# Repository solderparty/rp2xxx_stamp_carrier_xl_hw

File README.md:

# The RP2xxx Stamp Carrier Board XL

The RP2xxx Stamp Carrier XL, as the (somewhat long) name suggests, supports all the RP2-based Stamp boards. The Mega/Due form-factor ensures compatbility with many shields, including Uno ones. The wide range of connectors on the Carrier makes it a fully-fledged RP2xxx dev board.

The Carrier comes with a combo 3-in-1 SMD/TH/FlexyPin Stamp footprint, you can solder the Stamp directly to the Carrier, use 2mm pin headers + sockets to be able to plug it in and out, or use [FlexyPins](https://docs.solder.party/flexypin) to pop the Stamp in and out of the Carrier would soldering the Stamp. This way the Carrier also acts as a great Stamp flashing and testing jig. Check out the [Assembly Options](https://docs.solder.party/rp2xxx-stamp-carrier-xl/assembly_options) page for more details.

The board can be powered from the LiPo, over USB, or with a DC jack.

By using the RP2040 Stamp Carrier, you get everything that comes with the Stamp plus:

- USB Host and Device connectors with a toggle switch
- microSD socket
- Micro HDMI-shaped connector, connected to the HSTX peripheral
- SWD JST connector, compatible with the Raspberry Pi Pico Probe
- UART JST connector, compatible with the Raspberry Pi Pico Probe
- Qwiic connector
- 3.7/4.2V LiPo connector
- two user buttons
- PMOD header
- USR LED
- Power (3.3V) LED
- DC Jack

The DC Jack input is center-positive and supports voltages in the range of 7-12V. If you have the LiPo and either DC or USB connected, the battery will begin charging.

As mentioned above, the Carrier follows the Mega/Due/Uno shield pinout, making it compatible with a large ecosystem of shields, as long as they work on 3.3V IOs. **The pins are not 5V-tolerant**.

The CircuitPython firmware for the Stamps comes with a built-in board file for the Carrier, you can access it using `import stamp_carrier_board_xl as board`. After that, you can access all the Carrier pins and interfaces like you would with any other CPY board.

# Links

For more information visit https://rp2xxx-stamp-carrier-xl.solder.party/

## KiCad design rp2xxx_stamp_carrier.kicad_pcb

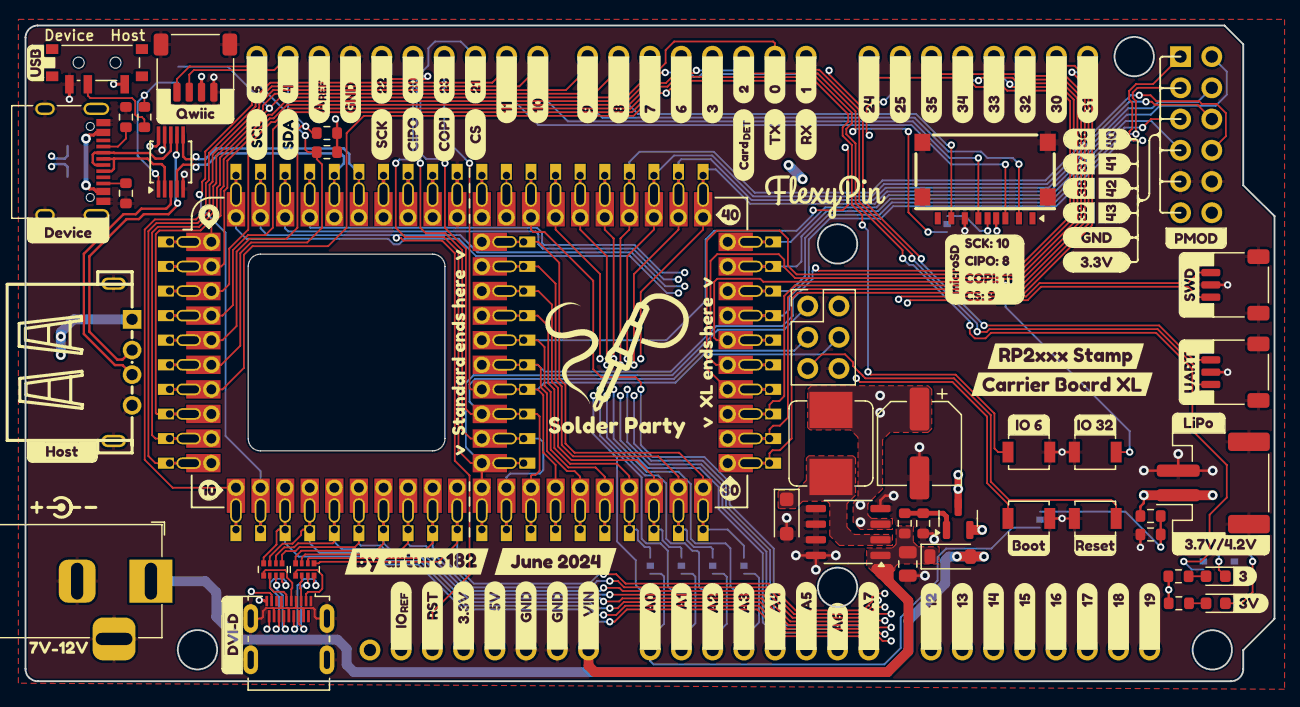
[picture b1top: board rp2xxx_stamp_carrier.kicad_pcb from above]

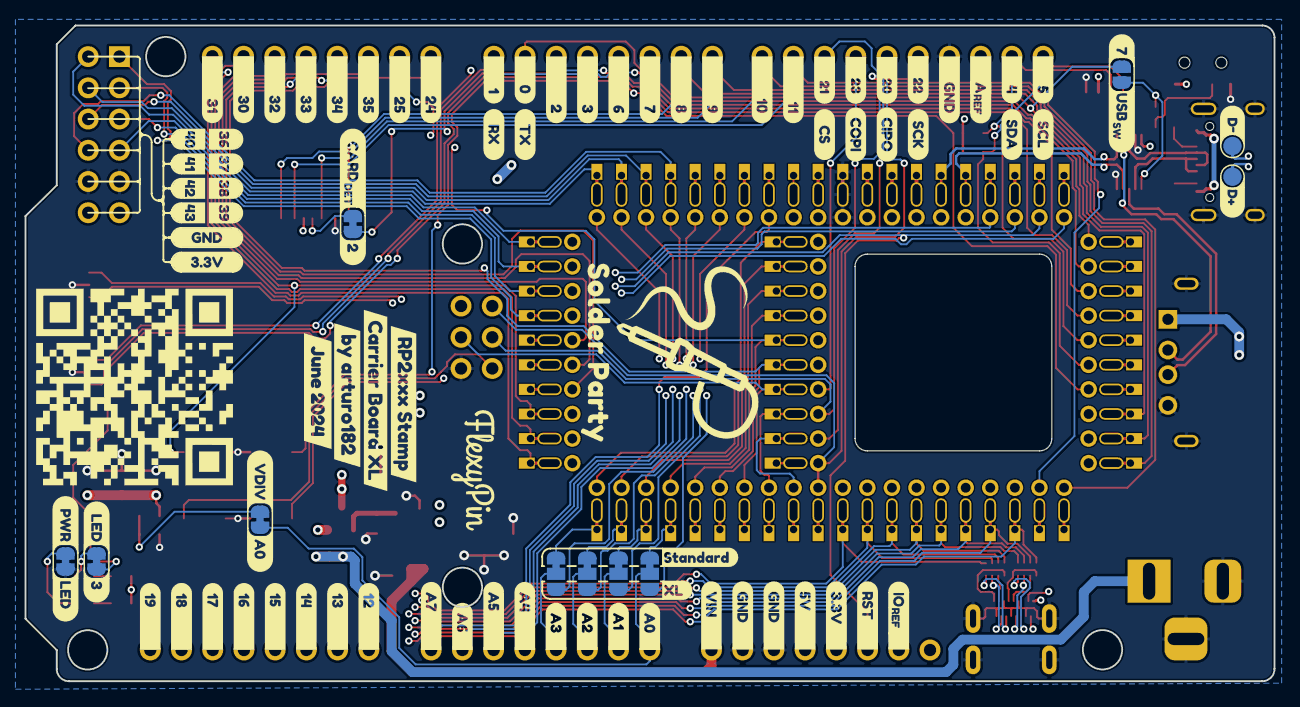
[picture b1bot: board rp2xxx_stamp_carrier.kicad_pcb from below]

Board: 4 copper layers, 101.6 x 53.3 mm, 255 parts (105 on the bottom side), 89 nets.

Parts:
C1: 22uF 25V; C_0805_2012Metric
C2: 100uF 25V; CP_Elec_6.3x4.9
D1: LED_USR; LED_0603_1608Metric
D2: 1N5819W; D_SOD-123
D3: DSS34; D_SOD-123F
D4: LED_PWR; LED_0603_1608Metric
J1: Conn_Qwiic; JST_SH_SM04B-SRSS-TB_1x04-1MP_P1.00mm_Horizontal
J2: Conn_Pi_SWD; JST_SH_SM03B-SRSS-TB_1x03-1MP_P1.00mm_Horizontal
J3: Conn_Pi_UART; JST_SH_SM03B-SRSS-TB_1x03-1MP_P1.00mm_Horizontal
J4: Conn_Batt; JST_PH_S2B-PH-SM4-TB_1x02-1MP_P2.00mm_Horizontal
J5: Barrel_Jack; BarrelJack_Horizontal
J6: DVI-D_Micro; HDMI_Micro-D_Molex_46765-1x01
J8: Conn_PMOD; PinSocket_2x06_P2.54mm_Vertical
J9, J12, J14, J15, J16: Conn_01x08; PinSocket_1x08_P2.54mm_Vertical
J10: Conn_01x10; PinSocket_1x10_P2.54mm_Vertical
J11: microSD; XUNPU_TF-123-ARP9Hxx
J13: Conn_SPI; PinHeader_2x03_P2.54mm_Vertical
J17: USB_C_Receptacle_USB2.0; USB_C_Receptacle_XKB_U262-16XN-4BVC11
J18: USB_A; USB_A_Receptacle_908-261A1011D10100
JP1: JP_VDIV; SolderJumper-2_P1.3mm_Bridged_RoundedPad1.0x1.5mm
JP2: JP_LED_USR; SolderJumper-2_P1.3mm_Bridged_RoundedPad1.0x1.5mm
JP3: JP_SD_DET; SolderJumper-2_P1.3mm_Bridged_RoundedPad1.0x1.5mm
JP4: JP_USB_SWITCH; SolderJumper-2_P1.3mm_Open_RoundedPad1.0x1.5mm
JP9: JP_LED_PWR; SolderJumper-2_P1.3mm_Bridged_RoundedPad1.0x1.5mm
JP10: SJ_A0; SolderJumper-3_P1.3mm_Bridged12_RoundedPad1.0x1.5mm
JP11: SJ_A1; SolderJumper-3_P1.3mm_Bridged12_RoundedPad1.0x1.5mm
JP12: SJ_A2; SolderJumper-3_P1.3mm_Bridged12_RoundedPad1.0x1.5mm
JP13: SJ_A3; SolderJumper-3_P1.3mm_Bridged12_RoundedPad1.0x1.5mm
L1: 47uH; L_Bourns_SRP7028A_7.3x6.6mm
Q1: DMG3415U-7; SOT-23
R1, R8: 1K; R_0603_1608Metric
R2, R3: 4.7K; R_0603_1608Metric
R4, R5, R6, R7, R11: 100K; R_0603_1608Metric
R9, R10: 5.1K; R_0603_1608Metric
RN1, RN2: 270R; R_Array_Convex_4x0402
SW1: BTN_RESET; SW_SPST_B3U-1000P
SW2: BTN_BOOTSEL; SW_SPST_B3U-1000P
SW3: SW_USB; SW_SPDT_PCM12
SW4: BTN_USR1; SW_SPST_B3U-1000P
SW5: BTN_USR2; SW_SPST_B3U-1000P
TP1: TP_USB_D+; TestPoint_Pad_D1.5mm
TP2: TP_USB_D-; TestPoint_Pad_D1.5mm
U1: XL1509-5.0; SOP-8_3.9x4.9mm_P1.27mm
U2: MSUSB30; MSOP-10_3x3mm_P0.5mm
U3: rp2xxx_Stamp_XL; RP2xx_Stamp_FlexyPin
kibuzzard-65DA3D92, kibuzzard-65DA3D92#2: G***; kibuzzard-65DA3D92
kibuzzard-65DA3D96, kibuzzard-65DA3D96#2: G***; kibuzzard-65DA3D96
kibuzzard-65DA3DCF: G***; kibuzzard-65DA3DCF
kibuzzard-65DA3ED0: G***; kibuzzard-65DA3ED0
kibuzzard-65DA3EE8, kibuzzard-65DA3EE8#2, kibuzzard-65DA3EE8#3, kibuzzard-65DA3EE8#4: G***; kibuzzard-65DA3EE8
kibuzzard-65DA13F9: G***; kibuzzard-65DA13F9
kibuzzard-65DA35ED: G***; kibuzzard-65DA35ED
kibuzzard-65DA43E4: G***; kibuzzard-65DA43E4
kibuzzard-65DA140C: G***; kibuzzard-65DA140C
kibuzzard-65DA141A: G***; kibuzzard-65DA141A
kibuzzard-65DA141E: G***; kibuzzard-65DA141E
kibuzzard-65DA143D: G***; kibuzzard-65DA143D
kibuzzard-65DA144D: G***; kibuzzard-65DA144D
kibuzzard-65DA145C: G***; kibuzzard-65DA145C
kibuzzard-65DA146D: G***; kibuzzard-65DA146D
kibuzzard-65DA148C: G***; kibuzzard-65DA148C
kibuzzard-65DA150C: G***; kibuzzard-65DA150C
kibuzzard-65DA150E: G***; kibuzzard-65DA150E
kibuzzard-65DA445F, kibuzzard-65DA445F#2: G***; kibuzzard-65DA445F
kibuzzard-65DA451B: G***; kibuzzard-65DA451B
kibuzzard-65DA451F: G***; kibuzzard-65DA451F
kibuzzard-65DA1408: G***; kibuzzard-65DA1408
kibuzzard-65DA1410: G***; kibuzzard-65DA1410
kibuzzard-65DA1413: G***; kibuzzard-65DA1413
kibuzzard-65DA1417: G***; kibuzzard-65DA1417
kibuzzard-65DA1440: G***; kibuzzard-65DA1440
kibuzzard-65DA1442: G***; kibuzzard-65DA1442
kibuzzard-65DA1448: G***; kibuzzard-65DA1448
kibuzzard-65DA1450: G***; kibuzzard-65DA1450
kibuzzard-65DA1453: G***; kibuzzard-65DA1453
kibuzzard-65DA1457: G***; kibuzzard-65DA1457
kibuzzard-65DA1460: G***; kibuzzard-65DA1460
kibuzzard-65DA1463: G***; kibuzzard-65DA1463
kibuzzard-65DA1466: G***; kibuzzard-65DA1466
kibuzzard-65DA1469: G***; kibuzzard-65DA1469
kibuzzard-65DA1470: G***; kibuzzard-65DA1470
kibuzzard-65DA1473: G***; kibuzzard-65DA1473
kibuzzard-65DA1483: G***; kibuzzard-65DA1483
kibuzzard-65DA1486: G***; kibuzzard-65DA1486
kibuzzard-65DA1492: G***; kibuzzard-65DA1492
kibuzzard-65DA1508: G***; kibuzzard-65DA1508
kibuzzard-65DA1511: G***; kibuzzard-65DA1511
kibuzzard-65DA1514: G***; kibuzzard-65DA1514
kibuzzard-65DA1517: G***; kibuzzard-65DA1517
kibuzzard-65DA4352: G***; kibuzzard-65DA4352
kibuzzard-65DA4391, kibuzzard-65DA4391#2, kibuzzard-65DA4391#3, kibuzzard-65DA4391#4: G***; kibuzzard-65DA4391
kibuzzard-65DA4455, kibuzzard-65DA4455#2: G***; kibuzzard-65DA4455
kibuzzard-65DA4463, kibuzzard-65DA4463#2: G***; kibuzzard-65DA4463
kibuzzard-65DA4468, kibuzzard-65DA4468#2: G***; kibuzzard-65DA4468
kibuzzard-65DA4513, kibuzzard-65DA4513#2: G***; kibuzzard-65DA4513
kibuzzard-65DA4517, kibuzzard-65DA4517#2: G***; kibuzzard-65DA4517
kibuzzard-65DB6F6F: G***; kibuzzard-65DB6F6F
kibuzzard-65DB8C3D: G***; kibuzzard-65DB8C3D
kibuzzard-65DB8C4A: G***; kibuzzard-65DB8C4A
kibuzzard-65DB8C5D: G***; kibuzzard-65DB8C5D
kibuzzard-65DB8C6C: G***; kibuzzard-65DB8C6C
kibuzzard-65DB8C35: G***; kibuzzard-65DB8C35
kibuzzard-65DB8C43: G***; kibuzzard-65DB8C43
kibuzzard-65DB8C55: G***; kibuzzard-65DB8C55
kibuzzard-65DB8C65: G***; kibuzzard-65DB8C65
kibuzzard-65DB8CB7: G***; kibuzzard-65DB8CB7
kibuzzard-65DB8EB0: G***; kibuzzard-65DB8EB0
kibuzzard-65DB9A5B: G***; kibuzzard-65DB9A5B
kibuzzard-65DB9AC9: G***; kibuzzard-65DB9AC9
kibuzzard-65DB9ADE: G***; kibuzzard-65DB9ADE
kibuzzard-65DB9BDD: G***; kibuzzard-65DB9BDD
kibuzzard-65DB9C6E: G***; kibuzzard-65DB9C6E
kibuzzard-65DB9FCE: G***; kibuzzard-65DB9FCE
kibuzzard-65DB9FED: G***; kibuzzard-65DB9FED
kibuzzard-65DB88A1: G***; kibuzzard-65DB88A1
kibuzzard-65DB90A8: G***; kibuzzard-65DB90A8
kibuzzard-65DB90AF: G***; kibuzzard-65DB90AF
kibuzzard-65DB90B6: G***; kibuzzard-65DB90B6
kibuzzard-65DB90CA: G***; kibuzzard-65DB90CA
kibuzzard-65DB92A0: G***; kibuzzard-65DB92A0
kibuzzard-65DB92A7: G***; kibuzzard-65DB92A7
kibuzzard-65DB92AF: G***; kibuzzard-65DB92AF
kibuzzard-65DB92BE: G***; kibuzzard-65DB92BE
kibuzzard-65DB92C6: G***; kibuzzard-65DB92C6
kibuzzard-65DB92CE: G***; kibuzzard-65DB92CE
kibuzzard-65DB92F8: G***; kibuzzard-65DB92F8
kibuzzard-65DB97A1: G***; kibuzzard-65DB97A1
kibuzzard-65DB97F6: G***; kibuzzard-65DB97F6
kibuzzard-65DB876F: G***; kibuzzard-65DB876F
kibuzzard-65DB884E: G***; kibuzzard-65DB884E
kibuzzard-65DB908D: G***; kibuzzard-65DB908D
kibuzzard-65DB909F: G***; kibuzzard-65DB909F
kibuzzard-65DB928A: G***; kibuzzard-65DB928A
kibuzzard-65DB931B: G***; kibuzzard-65DB931B
kibuzzard-65DB932B: G***; kibuzzard-65DB932B
kibuzzard-65DB8732: G***; kibuzzard-65DB8732
kibuzzard-65DB8845: G***; kibuzzard-65DB8845
kibuzzard-65DB8856: G***; kibuzzard-65DB8856
kibuzzard-65DB8860: G***; kibuzzard-65DB8860
kibuzzard-65DB9086: G***; kibuzzard-65DB9086
kibuzzard-65DB9096: G***; kibuzzard-65DB9096
kibuzzard-65DB9291: G***; kibuzzard-65DB9291
kibuzzard-65DB9299: G***; kibuzzard-65DB9299
kibuzzard-65DB9324: G***; kibuzzard-65DB9324
kibuzzard-65DBA05E: G***; kibuzzard-65DBA05E
kibuzzard-65DBA5ED: G***; kibuzzard-65DBA5ED
kibuzzard-65DBA047: G***; kibuzzard-65DBA047
kibuzzard-65DBA204: G***; kibuzzard-65DBA204
kibuzzard-65DBAB3B: G***; kibuzzard-65DBAB3B
kibuzzard-65DBAB4B: G***; kibuzzard-65DBAB4B
kibuzzard-65DBAB8B: G***; kibuzzard-65DBAB8B
kibuzzard-65DBAE3B: G***; kibuzzard-65DBAE3B
kibuzzard-65DBAE3E: G***; kibuzzard-65DBAE3E
kibuzzard-65DBAE42: G***; kibuzzard-65DBAE42
kibuzzard-65DBAE46: G***; kibuzzard-65DBAE46
kibuzzard-65DBAFC4: G***; kibuzzard-65DBAFC4
kibuzzard-65DBB0B8: G***; kibuzzard-65DBB0B8
kibuzzard-65DBB1B5: G***; kibuzzard-65DBB1B5
kibuzzard-65DBB3A0: G***; kibuzzard-65DBB3A0
kibuzzard-65DBB5CC: G***; kibuzzard-65DBB5CC
kibuzzard-65DBB07F: G***; kibuzzard-65DBB07F
kibuzzard-65DBB7FE: G***; kibuzzard-65DBB7FE
kibuzzard-65DBB28B: G***; kibuzzard-65DBB28B
kibuzzard-65DBB461: G***; kibuzzard-65DBB461
kibuzzard-65DBB727: G***; kibuzzard-65DBB727
kibuzzard-65DBBE17, kibuzzard-65DBBE17#2: G***; kibuzzard-65DBBE17
kibuzzard-65DBBE25, kibuzzard-65DBBE25#2: G***; kibuzzard-65DBBE25
kibuzzard-65DBBE65, kibuzzard-65DBBE65#2: G***; kibuzzard-65DBBE65
kibuzzard-65DBC04C: G***; kibuzzard-65DBC04C
kibuzzard-65DBC042: G***; kibuzzard-65DBC042
kibuzzard-65DBC046: G***; kibuzzard-65DBC046
kibuzzard-65DBC049: G***; kibuzzard-65DBC049
kibuzzard-65DBC50C: G***; kibuzzard-65DBC50C
kibuzzard-65DBC86E: G***; kibuzzard-65DBC86E
kibuzzard-65DBC416: G***; kibuzzard-65DBC416
kibuzzard-65DBC874: G***; kibuzzard-65DBC874
kibuzzard-65DBD3AD: G***; kibuzzard-65DBD3AD
kibuzzard-65DBD7D2, kibuzzard-65DBD7D2#2: G***; kibuzzard-65DBD7D2
kibuzzard-65DBD8C5, kibuzzard-65DBD8C5#2: G***; kibuzzard-65DBD8C5
kibuzzard-65DBD8CA, kibuzzard-65DBD8CA#2: G***; kibuzzard-65DBD8CA
kibuzzard-65DBD83D, kibuzzard-65DBD83D#2: G***; kibuzzard-65DBD83D
kibuzzard-65DBD87F, kibuzzard-65DBD87F#2: G***; kibuzzard-65DBD87F
kibuzzard-65DBD479: G***; kibuzzard-65DBD479
kibuzzard-65DBD837, kibuzzard-65DBD837#2: G***; kibuzzard-65DBD837
kibuzzard-65DBD847, kibuzzard-65DBD847#2: G***; kibuzzard-65DBD847
kibuzzard-65DBD875, kibuzzard-65DBD875#2: G***; kibuzzard-65DBD875
kibuzzard-65DBDBD8: G***; kibuzzard-65DBDBD8
kibuzzard-65DBDBE3: G***; kibuzzard-65DBDBE3
kibuzzard-65DBDBF9: G***; kibuzzard-65DBDBF9
kibuzzard-65DBDC20: G***; kibuzzard-65DBDC20
kibuzzard-65DBDC23: G***; kibuzzard-65DBDC23
kibuzzard-668C75B1: G***; kibuzzard-668C75B1
kibuzzard-668C75C6: G***; kibuzzard-668C75C6
kibuzzard-668C75DA: G***; kibuzzard-668C75DA
kibuzzard-668C76A7: G***; kibuzzard-668C76A7
kibuzzard-668C88D6: G***; kibuzzard-668C88D6
kibuzzard-668C88F2: G***; kibuzzard-668C88F2
kibuzzard-668C89D9: G***; kibuzzard-668C89D9
kibuzzard-668C97F2: G***; kibuzzard-668C97F2
kibuzzard-668C7671: G***; kibuzzard-668C7671
kibuzzard-668C7736: G***; kibuzzard-668C7736
kibuzzard-668C7740: G***; kibuzzard-668C7740
kibuzzard-668C7764: G***; kibuzzard-668C7764
kibuzzard-668C8744: G***; kibuzzard-668C8744
kibuzzard-668C9122: G***; kibuzzard-668C9122
kibuzzard-668C9635: G***; kibuzzard-668C9635
kibuzzard-6695ACF2: G***; kibuzzard-6695ACF2
kibuzzard-6695AD18: G***; kibuzzard-6695AD18
kibuzzard-6695BF60: G***; kibuzzard-6695BF60
kibuzzard-6695BFEA: G***; kibuzzard-6695BFEA
kibuzzard-6695CF81: G***; kibuzzard-6695CF81
kibuzzard-6695CF95: G***; kibuzzard-6695CF95
kibuzzard-660639E8: G***; kibuzzard-660639E8
kibuzzard-660639F3: G***; kibuzzard-660639F3
kibuzzard-669714D3: G***; kibuzzard-669714D3
kibuzzard-66063958: G***; kibuzzard-66063958
kibuzzard-66063979: G***; kibuzzard-66063979
svg2mod: G***; svg2mod

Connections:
+3.3V: J1.2, J8.11, J8.12, J9.2, J9.4, J10.3, J11.4 (VDD), R1.1, R2.1, R3.1, R8.1, SW3.1 (A), U2.10 (VDD), U3.34 (3.3V)
+5V: C2.1, J6.19 (+5V), J9.5, J13.2, J18.1 (VBUS), L1.2, Q1.2 (S), U1.3 (FB), U3.33 (5V)
+BATT: J4.1, R4.1, U3.32 (VBAT)
/A0: J12.1, JP1.2 (B), JP10.2 (C)
/A0_{A}: JP10.1 (A), U3.27 (GPIO26)
/A0_{B}: J8.2, JP10.3 (B), U3.51 (GPIO40)
/A1: J12.2, JP11.2 (C)
/A1_{A}: JP11.1 (A), U3.28 (GPIO27)
/A1_{B}: J8.4, JP11.3 (B), U3.52 (GPIO41)
/A2: J12.3, JP12.2 (C)
/A2_{A}: JP12.1 (A), U3.29 (GPIO28)
/A2_{B}: J8.6, JP12.3 (B), U3.53 (GPIO42)
/A3: J12.4, JP13.2 (C)
/A3_{A}: JP13.1 (A), U3.30 (GPIO29)
/A3_{B}: J8.8, JP13.3 (B), U3.54 (GPIO43)
/A4: J12.5, U3.55 (GPIO44)
/A5: J12.6, U3.56 (GPIO45)
/A6: J12.7, U3.57 (GPIO46)
/A7: J12.8, U3.58 (GPIO47)
/BOOTSEL: SW2.2 (B), U3.40 (BOOTSEL)
/BTN_USR1: J14.4, SW4.2 (B), U3.7 (GPIO6)
/BTN_USR2: J16.6, SW5.2 (B), U3.43 (GPIO32)
/CARD_DET: J14.6, JP3.2 (B), U3.3 (GPIO2)
/CIPO0: J10.6, J13.1, U3.21 (GPIO20)
/CIPO1: J11.7 (DAT0), J14.2, U3.9 (GPIO8)
/COPI0: J10.7, J13.4, U3.24 (GPIO23)
/COPI1: J10.9, J11.3 (CMD), U3.12 (GPIO11)
/CS0: J10.8, U3.22 (GPIO21)
/CS1: J11.2 (DAT3/CD), J14.1, U3.10 (GPIO9)
/GPIO0: J3.3, J14.7, U3.1 (GPIO0)
/GPIO1: J3.1, J14.8, U3.2 (GPIO1)
/GPIO3: J14.5, JP2.2 (B), U3.4 (GPIO3)
/GPIO4: J1.3, J6.18 (SDA), J10.2, R3.2, U3.5 (GPIO4)
/GPIO5: J1.4, J6.17 (SCL), J10.1, R2.2, U3.6 (GPIO5)
/GPIO7: J14.3, JP4.2 (B), U3.8 (GPIO7)
/GPIO10: J10.10, J11.5 (CLK), U3.11 (GPIO10)
/GPIO12: J15.1, RN2.8 (R1.2), U3.13 (GPIO12)
/GPIO13: J15.2, RN2.7 (R2.2), U3.14 (GPIO13)
/GPIO14: J15.3, RN2.6 (R3.2), U3.15 (GPIO14)
/GPIO15: J15.4, RN2.5 (R4.2), U3.16 (GPIO15)
/GPIO16: J15.5, RN1.8 (R1.2), U3.17 (GPIO16)
/GPIO17: J15.6, RN1.7 (R2.2), U3.18 (GPIO17)
/GPIO18: J15.7, RN1.6 (R3.2), U3.19 (GPIO18)
/GPIO19: J15.8, RN1.5 (R4.2), U3.20 (GPIO19)
/GPIO22: J10.5, J13.3, U3.23 (GPIO22)
/GPIO24: J16.1, U3.25 (GPIO24)
/GPIO25: J16.2, U3.26 (GPIO25)
/GPIO30: J16.7, U3.41 (GPIO30)
/GPIO31: J16.8, U3.42 (GPIO31)
/GPIO33: J16.5, U3.44 (GPIO33)
/GPIO34: J16.4, U3.45 (GPIO34)
/GPIO35: J16.3, U3.46 (GPIO35)
/GPIO36: J8.1, U3.47 (GPIO36)
/GPIO37: J8.3, U3.48 (GPIO37)
/GPIO38: J8.5, U3.49 (GPIO38)
/GPIO39: J8.7, U3.50 (GPIO39)
/SWCLK: J2.1, U3.38 (SWCLK)
/SWDIO: J2.3, U3.37 (SWDIO)
/USB/USB_A_D+: J18.3 (D+), U2.3 (HSD2+)
/USB/USB_A_D-: J18.2 (D-), U2.7 (HSD2-)
/USB/USB_C_D+: J17.A6 (D+), J17.B6 (D+), U2.2 (HSD1+)
/USB/USB_C_D-: J17.A7 (D-), J17.B7 (D-), U2.8 (HSD1-)
/USB_D+: TP1.1, U2.4 (D+), U3.36 (USB_D+)
/USB_D-: TP2.1, U2.6 (D-), U3.35 (USB_D-)
/~RESET: J9.3, J13.5, SW1.2 (B), U3.39 (~RESET)
GND: C1.1, C2.2, D3.2 (A), J1.1, J2.2, J3.2, J4.2, J5.2, J5.3, J6.4 (D2S), J6.7 (D1S), J6.10 (D0S), J6.13 (CKS), J6.16 (GND), J6.SH, J8.9, J8.10, J9.6, J9.7, J10.4, J11.6 (VSS), J11.11 (SHIELD), J13.6, J17.A1 (GND), J17.A12 (GND), J17.B1 (GND), J17.B12 (GND), J17.S1 (SHIELD), J18.4 (GND), J18.5 (Shield), JP9.2 (B), R5.2, R7.2, R9.2, R10.2, SW1.1 (A), SW2.1 (A), SW3.3 (C), SW4.1 (A), SW5.1 (A), U1.4 (EN), U1.5 (GND), U1.6 (GND), U1.7 (GND), U1.8 (GND), U2.5 (GND), U2.9 (~OE), U3.31 (GND)
unnamed: D1.2 (A), R1.2
unnamed: D1.1 (K), JP2.1 (A)
unnamed: D3.1 (K), L1.1, U1.2 (OUT)
unnamed: D4.2 (A), R8.2
unnamed: D4.1 (K), JP9.1 (A)
unnamed: J6.12 (CK+), RN2.3 (R3.1)
unnamed: J6.14 (CK-), RN2.4 (R4.1)
unnamed: J6.9 (D0+), RN2.1 (R1.1)
unnamed: J6.11 (D0-), RN2.2 (R2.1)
unnamed: J6.6 (D1+), RN1.3 (R3.1)
unnamed: J6.8 (D1-), RN1.4 (R4.1)
unnamed: J6.3 (D2+), RN1.1 (R1.1)
unnamed: J6.5 (D2-), RN1.2 (R2.1)
unnamed: J11.9 (DET_B), JP3.1 (A)
unnamed: J17.A5 (CC1), R9.1
unnamed: J17.B5 (CC2), R10.1
unnamed: JP1.1 (A), R4.2, R5.1
unnamed: JP4.1 (A), R11.2, U2.1 (S)
unnamed: Q1.1 (G), R6.2, R7.1
unnamed: R11.1, SW3.2 (B)
VBUS: J17.A4 (VBUS), J17.A9 (VBUS), J17.B4 (VBUS), J17.B9 (VBUS), Q1.3 (D)
VDC: D2.2 (A), J5.1
VIN: C1.2, D2.1 (K), J9.8, R6.1, U1.1 (IN)

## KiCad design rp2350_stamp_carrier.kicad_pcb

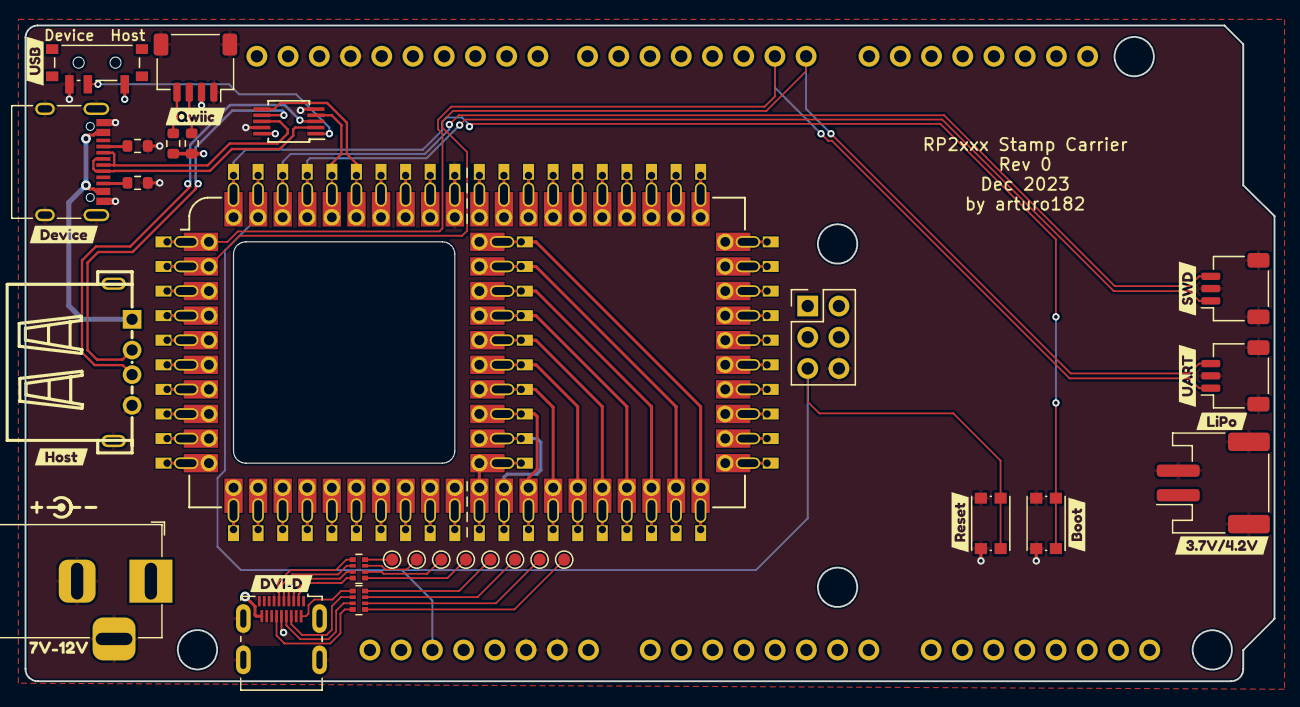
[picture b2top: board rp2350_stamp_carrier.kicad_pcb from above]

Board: 4 copper layers, 101.6 x 53.3 mm, 46 parts (0 on the bottom side), 39 nets.

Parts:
J1: Conn_02x30_Counter_Clockwise; RP2xx_Stamp_FlexyPin
J2: Conn_01x10; PinSocket_1x10_P2.54mm_Vertical
J3, J4, J5, J6, J7: Conn_01x08; PinSocket_1x08_P2.54mm_Vertical
J8: Conn_SPI; PinHeader_2x03_P2.54mm_Vertical
J10: Barrel_Jack; BarrelJack_Horizontal
J11: Conn_Batt; JST_PH_S2B-PH-SM4-TB_1x02-1MP_P2.00mm_Horizontal
J12: Conn_Stemma_QT; JST_SH_SM04B-SRSS-TB_1x04-1MP_P1.00mm_Horizontal
J13: USB_C_Receptacle_USB2.0; USB_C_Receptacle_XKB_U262-16XN-4BVC11
J14: Conn_Pi_SWD; JST_SH_SM03B-SRSS-TB_1x03-1MP_P1.00mm_Horizontal
J15: Conn_Pi_UART; JST_SH_SM03B-SRSS-TB_1x03-1MP_P1.00mm_Horizontal
J17: USB_A; USB_A_Receptacle_908-261A1011D10100
J18: HDMI_C_1.4; HDMI_Micro-D_Molex_46765-1x01
R1, R4: 5.1K; R_0603_1608Metric
R2, R3: 4.7K; R_0603_1608Metric
RN1, RN2: 270R; R_Array_Convex_4x0402
SW1, SW2: BTN_UP; SW_Push_1P1T_NO_CK_KMR2
SW3: SW_USB; SW_SPDT_PCM12
TP1, TP2, TP3, TP4, TP5, TP6, TP7, TP8: TestPoint; TestPoint_Pad_D1.0mm
U2: MSUSB30; MSOP-10_3x3mm_P0.5mm
kibuzzard-6575ECE3: G***; kibuzzard-6575ECE3
kibuzzard-657528E6: G***; kibuzzard-657528E6
kibuzzard-657528F6: G***; kibuzzard-657528F6
kibuzzard-657529A9: G***; kibuzzard-657529A9
kibuzzard-657529B8: G***; kibuzzard-657529B8
kibuzzard-657529FD: G***; kibuzzard-657529FD
kibuzzard-6575292F: G***; kibuzzard-6575292F
kibuzzard-6575299A: G***; kibuzzard-6575299A
kibuzzard-65752916: G***; kibuzzard-65752916
kibuzzard-65752919: G***; kibuzzard-65752919
kibuzzard-65752924: G***; kibuzzard-65752924
svg2mod: G***; svg2mod

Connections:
+3V3: J1.34, J2.3, J5.2, J5.4, J12.2, R2.1, R3.1, SW3.1 (A), U2.10 (VDD)
+5V: J1.33, J5.5, J8.2, J18.18 (+5V)
/BOOTSEL: J1.40, SW2.2 (B)
/CK+: J18.11 (CK+), RN1.1 (R1.1)
/CK-: J18.12 (CK-), RN2.4 (R4.1)
/D0+: J18.8 (D0+), RN2.3 (R3.1)
/D0-: J18.9 (D0-), RN1.2 (R2.1)
/D0/RX: J1.2, J3.8, J15.3
/D1+: J18.5 (D1+), RN1.3 (R3.1)
/D1-: J18.6 (D1-), RN2.2 (R2.1)
/D1/TX: J1.1, J3.7, J15.1
/D2+: J18.2 (D2+), RN2.1 (R1.1)
/D2-: J18.3 (D2-), RN1.4 (R4.1)
/D20/SDA: J2.2, J4.7
/D21/SCL: J2.1, J4.8
/SWCLK: J1.38, J14.3
/SWDIO: J1.37, J14.1
/USB/USB_A_D+: J17.3 (D+), U2.3 (HSD2+)
/USB/USB_A_D-: J17.2 (D-), U2.7 (HSD2-)
/USB/USB_C_D+: J13.A6 (D+), J13.B6 (D+), U2.2 (HSD1+)
/USB/USB_C_D-: J13.A7 (D-), J13.B7 (D-), U2.8 (HSD1-)
/USB_D+: J1.36, U2.4 (D+)
/USB_D-: J1.35, U2.6 (D-)
/~RESET: J1.39, J5.3, J8.5, SW1.2 (B)
GND: J1.31, J2.4, J5.6, J5.7, J8.6, J10.2, J10.3, J11.2, J12.1, J13.A1 (GND), J13.A12 (GND), J13.B1 (GND), J13.B12 (GND), J13.S1 (SHIELD), J14.2, J15.2, J17.4 (GND), J17.5 (Shield), J18.1 (D2S), J18.4 (D1S), J18.7 (D0S), J18.10 (CKS), J18.13 (GND), J18.SH, R1.2, R4.2, SW1.1 (A), SW2.1 (A), SW3.3 (C), U2.5 (GND), U2.9 (~OE)
unnamed: J12.3, R3.2
unnamed: J12.4, R2.2
unnamed: J13.A5 (CC1), R1.1
unnamed: J13.B5 (CC2), R4.1
unnamed: RN1.8 (R1.2), TP1.1
unnamed: RN1.7 (R2.2), TP2.1
unnamed: RN1.6 (R3.2), TP3.1
unnamed: RN1.5 (R4.2), TP4.1
unnamed: RN2.8 (R1.2), TP5.1
unnamed: RN2.7 (R2.2), TP6.1
unnamed: RN2.6 (R3.2), TP7.1
unnamed: RN2.5 (R4.2), TP8.1
unnamed: SW3.2 (B), U2.1 (S)
VBUS: J13.A4 (VBUS), J13.A9 (VBUS), J13.B4 (VBUS), J13.B9 (VBUS), J17.1 (VBUS)

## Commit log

2023-12-13 Rev 0
2024-02-26 Rev 1
2024-03-29 Rev 2
    Fixed HDMI connector
    Swapped RST and BOOTSEL buttons to match Stamp
    Added BAT_STAT to Stamp
    Changed 2x silk back to single line
    Adjusted Name silkscreen
2024-07-16 Rev 3
    - USB Switch jumper open by default
    - Power USB Host from 5V not VBUS
    - Fix SPI pin silkscreen
    - Add test points for USB D+/D-
2024-10-01 Rev 3.1, add README, and LICENSE
    - Fixed the microSD pin silkscreen
    - Updated BOM
